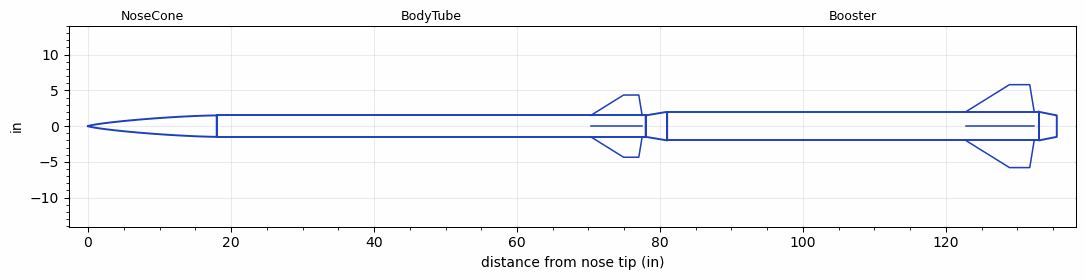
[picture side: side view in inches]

<RASAeroDocument>
 <FileVersion>2</FileVersion>
 <RocketDesign>
  <NoseCone>
   <Length>18</Length>
   <Diameter>3</Diameter>
   <Shape>Von Karman Ogive</Shape>
   <Location>0</Location>
  </NoseCone>
  <BodyTube>
   <Length>60</Length>
   <Diameter>3</Diameter>
   <Location>18</Location>
   <Fin>
    <Count>4</Count>
    <Chord>7.1775</Chord>
    <Span>2.85</Span>
    <SweepDistance>4.579</SweepDistance>
    <TipChord>2.13</TipChord>
    <Thickness>0.5</Thickness>
    <LERadius>0.08</LERadius>
    <Location>7.6725</Location>
    <AirfoilSection>Hexagonal</AirfoilSection>
    <FX1>0.5</FX1>
    <FX3>0.5</FX3>
   </Fin>
  </BodyTube>
  <Booster>
   <Length>52</Length>
   <Diameter>4</Diameter>
   <InsideDiameter>3</InsideDiameter>
   <Location>78</Location>
   <ShoulderLength>3</ShoulderLength>
   <BoattailLength>2.5</BoattailLength>
   <BoattailRearDiameter>3</BoattailRearDiameter>
   <Fin>
    <Count>4</Count>
    <Chord>9.57</Chord>
    <Span>3.8</Span>
    <SweepDistance>6.11</SweepDistance>
    <TipChord>2.84</TipChord>
    <Thickness>0.25</Thickness>
    <LERadius>0.08</LERadius>
    <Location>10.23</Location>
    <AirfoilSection>Hexagonal</AirfoilSection>
    <FX1>0.5</FX1>
    <FX3>0.5</FX3>
   </Fin>
  </Booster>
  <Surface>Rough Camouflage Paint</Surface>
  <ModifiedBarrowman>False</ModifiedBarrowman>
  <Turbulence>False</Turbulence>
  <UseBooster1>False</UseBooster1>
  <UseBooster2>False</UseBooster2>
 </RocketDesign>
 <LaunchSite>
  <Altitude>3000</Altitude>
  <Pressure>0</Pressure>
  <RodAngle>2</RodAngle>
  <RodLength>18</RodLength>
  <Temperature>85</Temperature>
  <WindSpeed>8</WindSpeed>
 </LaunchSite>
 <Recovery>
  <Altitude1>1000</Altitude1>
  <Altitude2>1000</Altitude2>
  <DeviceType1>None</DeviceType1>
  <DeviceType2>None</DeviceType2>
  <Event1>False</Event1>
  <Event2>False</Event2>
  <Size1>1</Size1>
  <Size2>1</Size2>
  <EventType1>None</EventType1>
  <EventType2>None</EventType2>
  <CD1>1.33</CD1>
  <CD2>1.33</CD2>
 </Recovery>
 <SimulationList>
  <Simulation>
   <SustainerEngine>M-1852  (M-1852)</SustainerEngine>
   <SustainerLaunchWt>25</SustainerLaunchWt>
   <SustainerNozzleDiameter>2.8</SustainerNozzleDiameter>
   <SustainerCG>34.07</SustainerCG>
   <SustainerIgnitionDelay>5</SustainerIgnitionDelay>
   <Booster1Engine>N-2857  (N-2857)</Booster1Engine>
   <Booster1LaunchWt>61.9</Booster1LaunchWt>
   <Booster1SeparationDelay>0</Booster1SeparationDelay>
   <Booster1IgnitionDelay>0</Booster1IgnitionDelay>
   <Booster1CG>56.47</Booster1CG>
   <Booster1NozzleDiameter>2.65</Booster1NozzleDiameter>
   <IncludeBooster1>True</IncludeBooster1>
   <Booster2Delay>0</Booster2Delay>
   <IncludeBooster2>False</IncludeBooster2>
   <TimetoApogee>54.02767</TimetoApogee>
   <MaxAltitude>47769.89</MaxAltitude>
   <MaxVelocity>2651.042</MaxVelocity>
  </Simulation>
 </SimulationList>
</RASAeroDocument>
